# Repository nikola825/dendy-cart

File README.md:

# Programmable cartridge for Dendy-style consoles

Programmable PLD-based cartrige for Dendy-like consoles.

## Features
1. 1MB of SRAM for use as PRG ROM or PRG RAM
2. 1MB of SRAM for use as CHR ROM or CHR RAM
3. Atmel ATF1508 CPLD for glue logic, mapper implementation and flashing
4. LM66100 and a CR2032 battery holder to allow RAM to act as non-volatile storage
5. JTAG header for CPLD flashing

## Tooling
Makefile and linker configuration for writing programs
Pattern table generator script to generate pattern table contents from bitmaps

## Repo contents
cart - Kicad project and BOM
verilog - Verilog code for the ATF1508 CPLD
6502_development/demo_program - demo code for writing programs
6502_development/bmptransform - python script to generate pattern table contents from bmp images

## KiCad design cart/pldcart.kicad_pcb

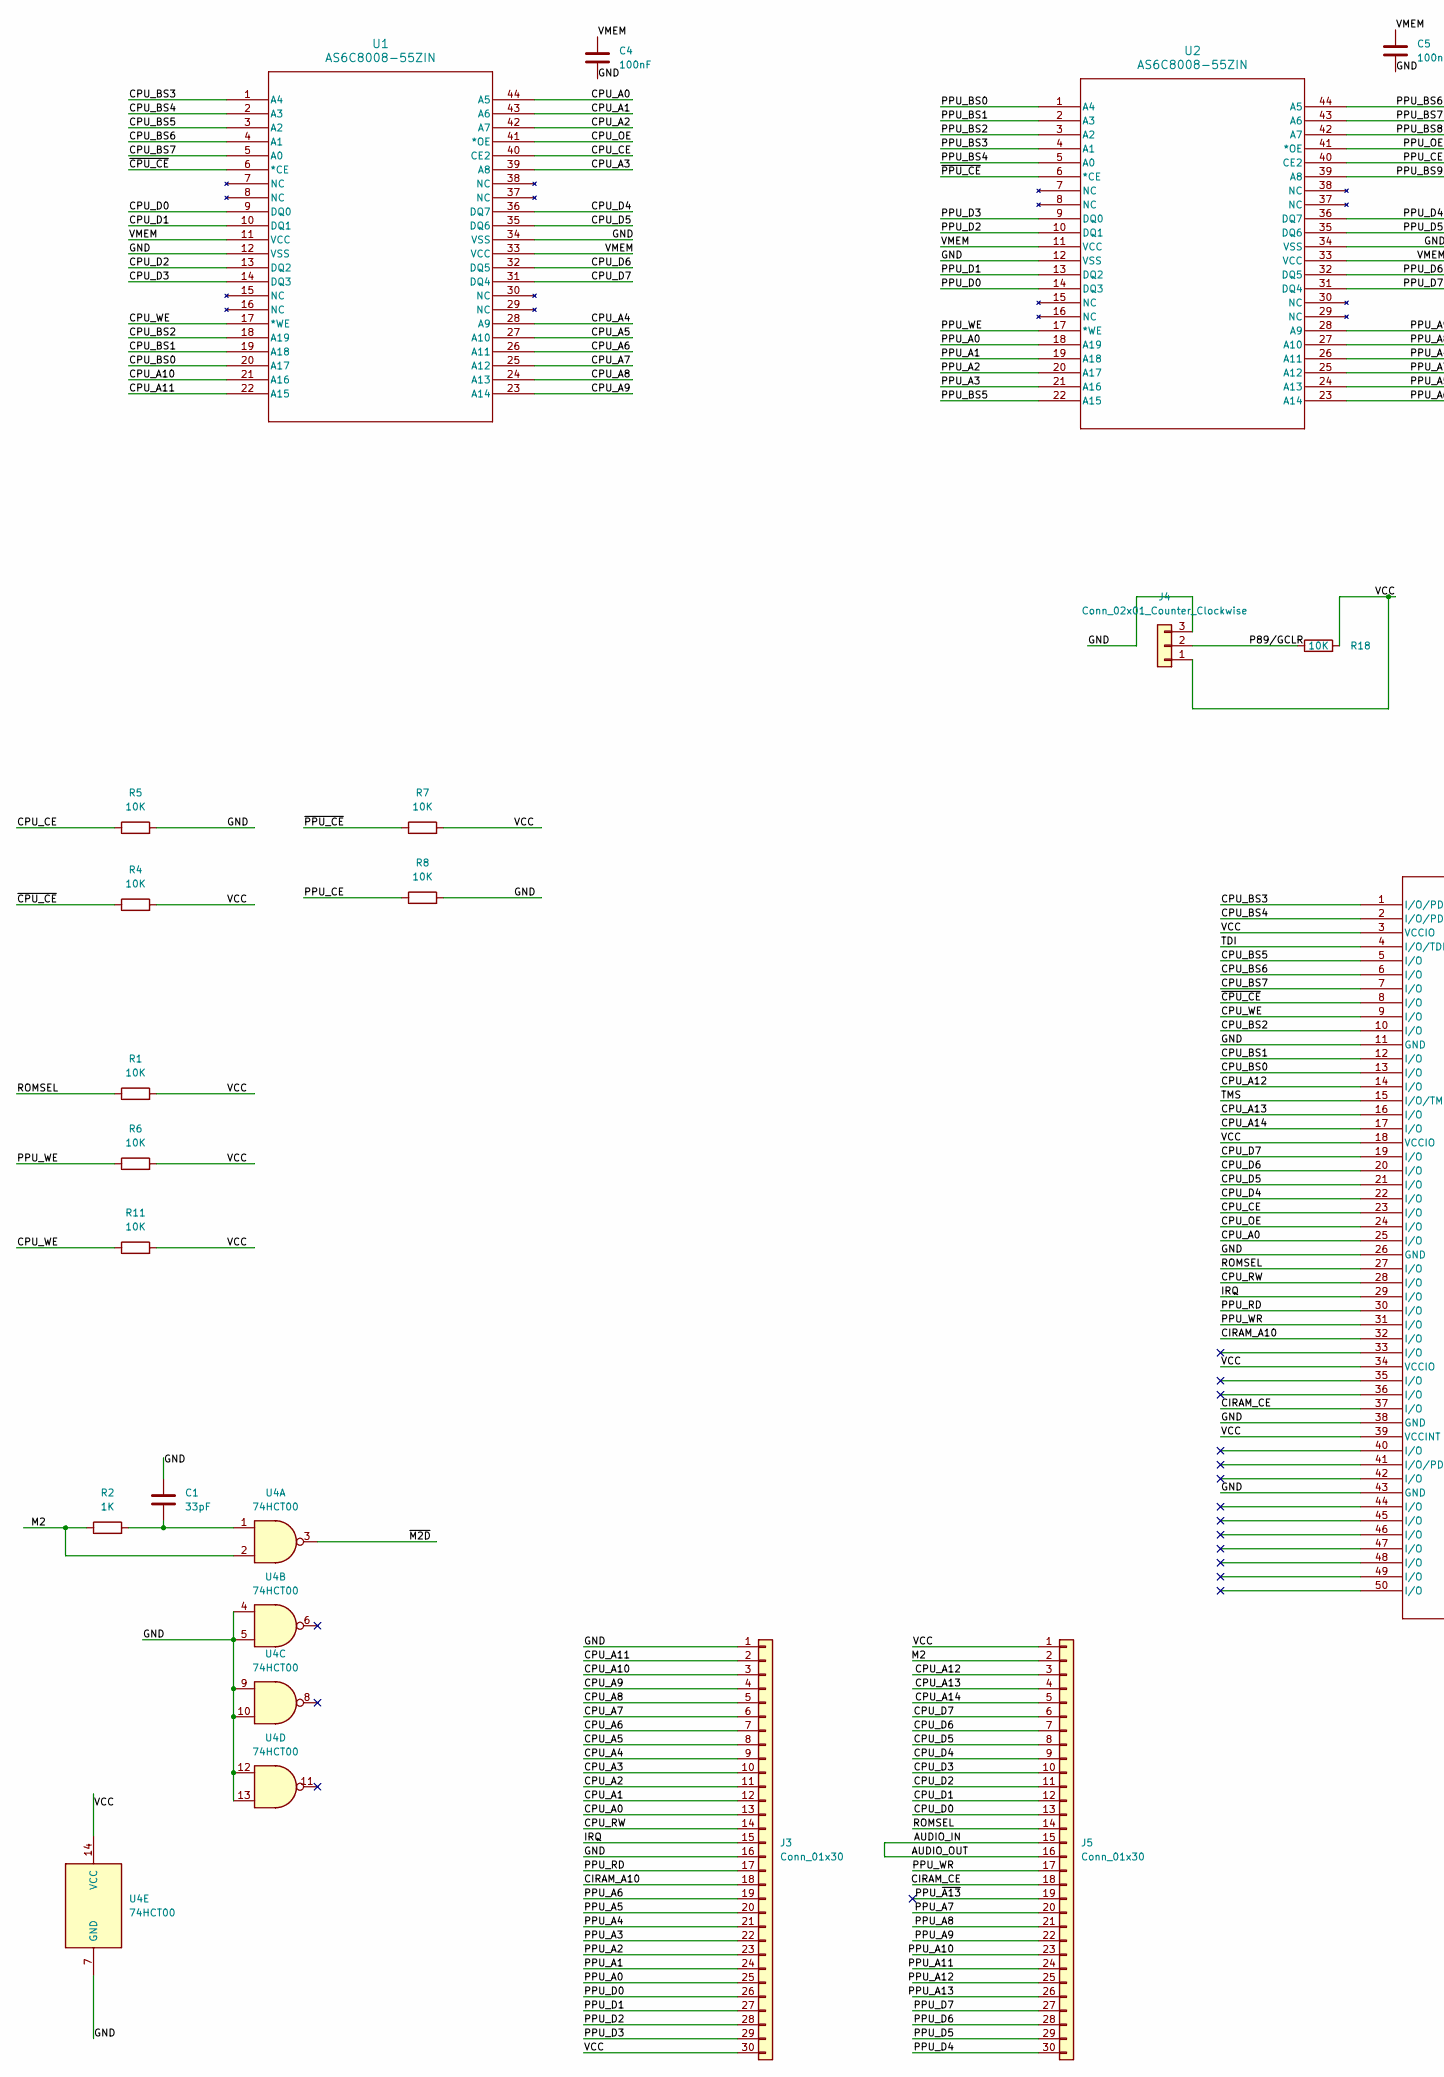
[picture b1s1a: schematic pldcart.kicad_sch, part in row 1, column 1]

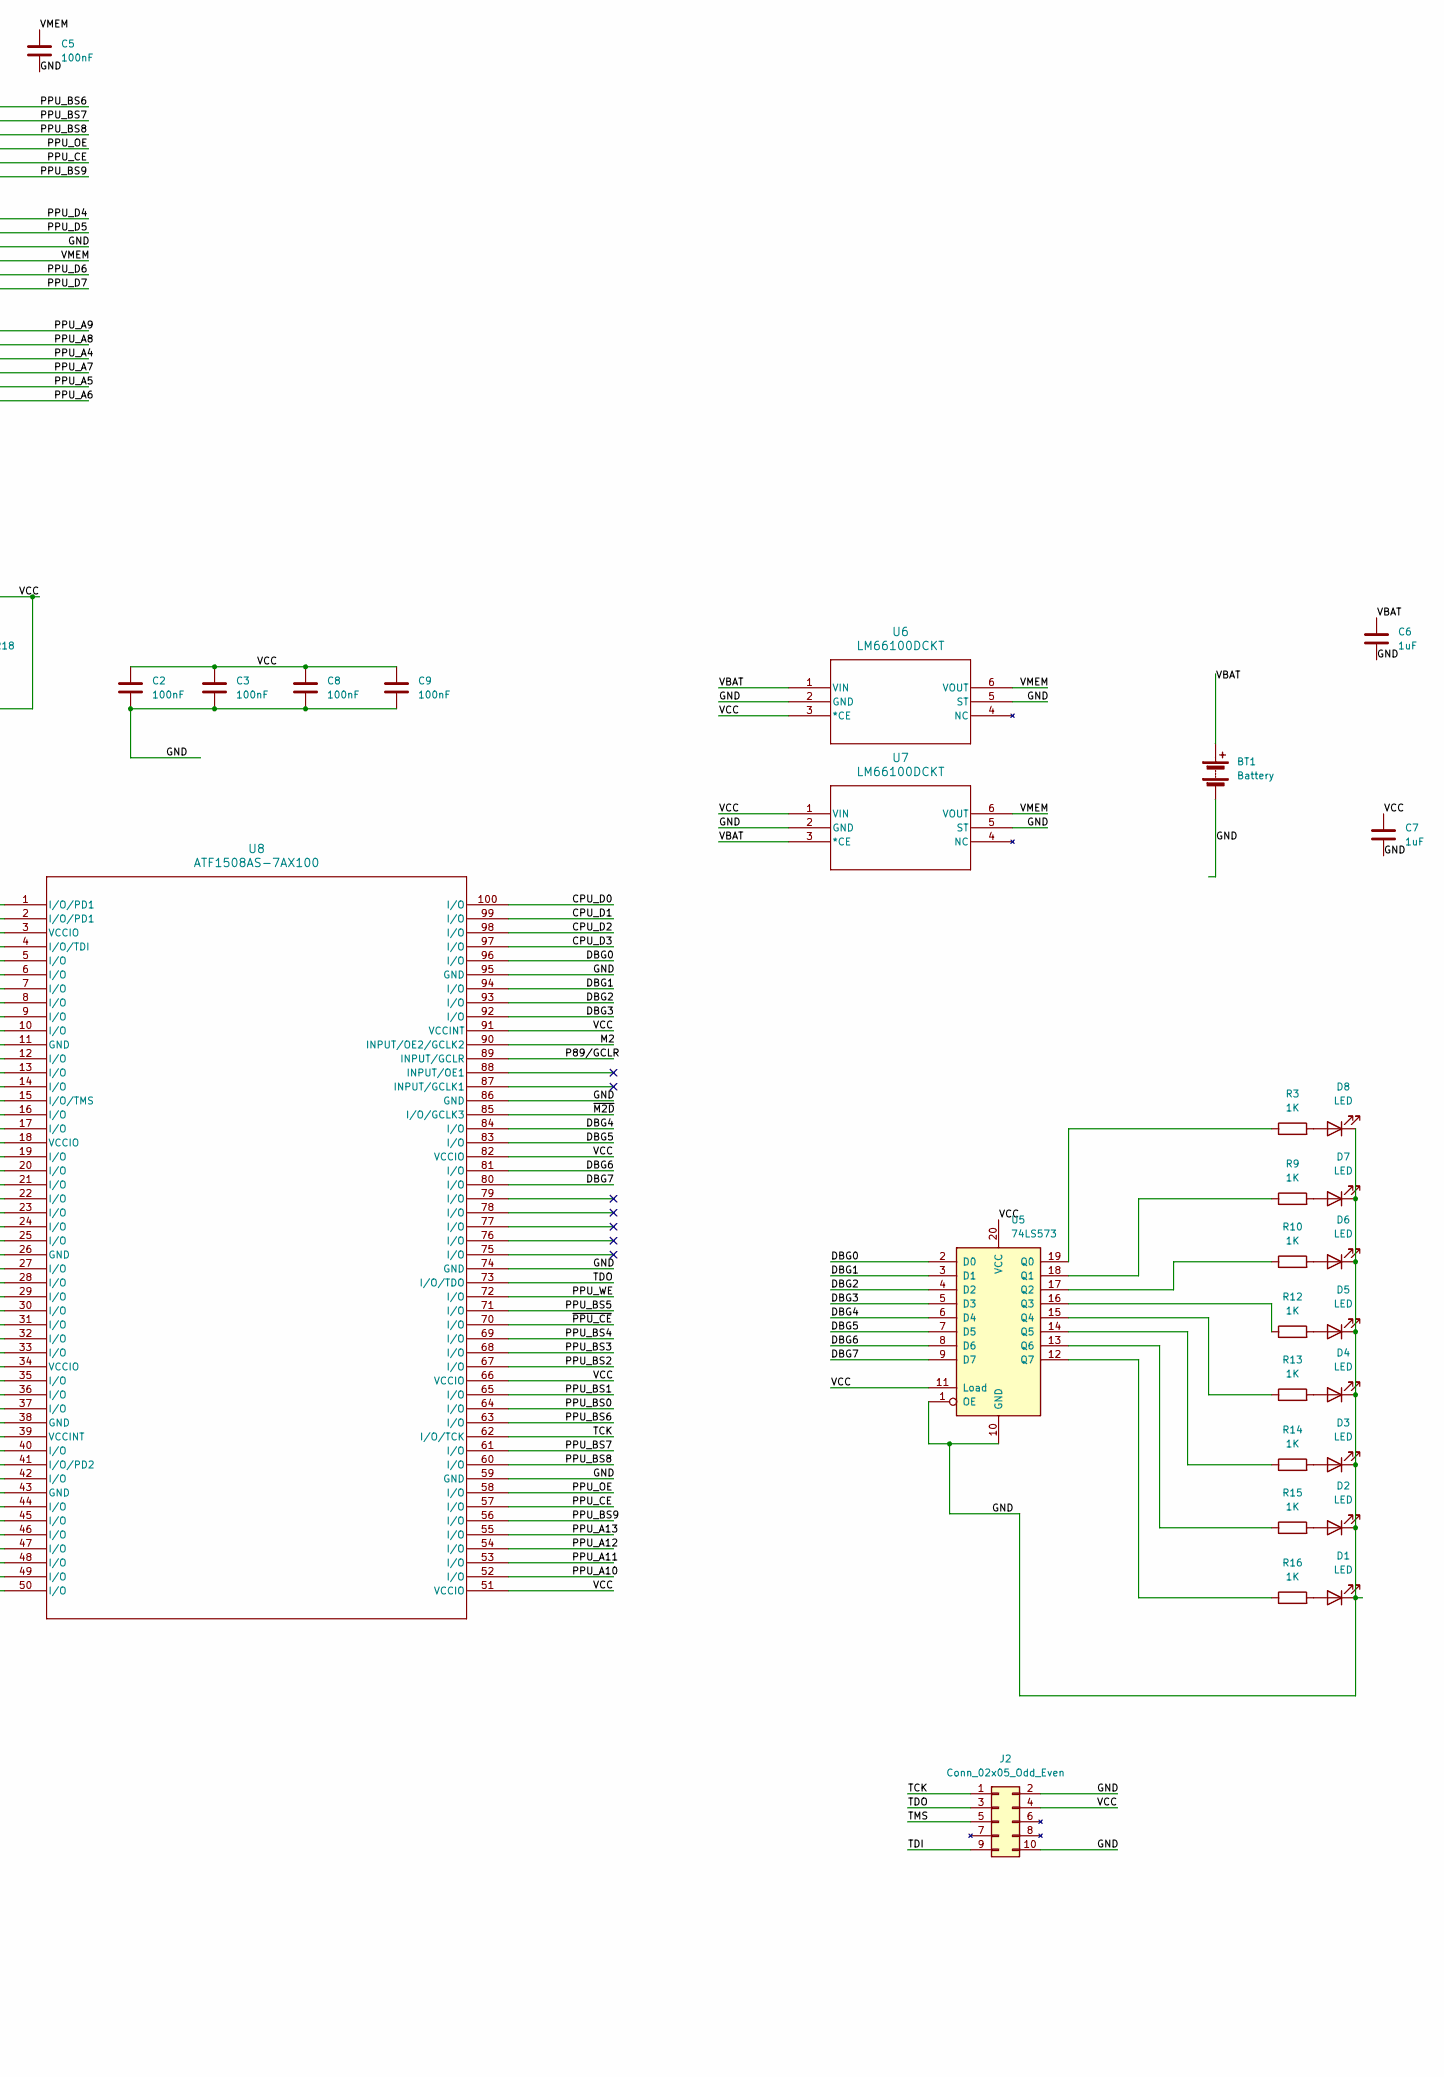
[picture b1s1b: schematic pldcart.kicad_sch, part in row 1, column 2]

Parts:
BT1: Battery; BatteryHolder_Keystone_103_1x20mm
C1: 33pF; C_0603_1608Metric
C2, C3, C4, C5, C8, C9: 100nF; C_0603_1608Metric
C6, C7: 1uF; C_0805_2012Metric
D1, D2, D3, D4, D5, D6, D7, D8: LED; LED_0603_1608Metric
J2: Conn_02x05_Odd_Even; PinHeader_2x05_P2.54mm_Vertical
J3, J5: Conn_01x30; PinHeader_1x30_P2.54mm_Vertical
J4: Conn_02x01_Counter_Clockwise; PinHeader_1x03_P2.54mm_Vertical
R1, R4, R5, R6, R7, R8, R11, R18: 10K; R_0603_1608Metric
R2, R3, R9, R10, R12, R13, R14, R15, R16: 1K; R_0603_1608Metric
U1, U2: AS6C8008-55ZIN; TSOP-II-44_10.16x18.41mm_P0.8mm
U4: 74HCT00; TSSOP-14_4.4x5mm_P0.65mm
U5: 74LS573; TSSOP-20_4.4x6.5mm_P0.65mm
U6, U7: LM66100DCKT; SOT-363_SC-70-6
U8: ATF1508AS-7AX100; TQFP-100_14x14mm_P0.5mm

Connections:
/AUDIO_IN: J5.15, J5.16
/CIRAM_A10: J3.18, U8.32 (I/O)
/CIRAM_CE: J5.18, U8.37 (I/O)
/CPU_A0: J3.13, U1.44 (A5), U8.25 (I/O)
/CPU_A1: J3.12, U1.43 (A6)
/CPU_A2: J3.11, U1.42 (A7)
/CPU_A3: J3.10, U1.39 (A8)
/CPU_A4: J3.9, U1.28 (A9)
/CPU_A5: J3.8, U1.27 (A10)
/CPU_A6: J3.7, U1.26 (A11)
/CPU_A7: J3.6, U1.25 (A12)
/CPU_A8: J3.5, U1.24 (A13)
/CPU_A9: J3.4, U1.23 (A14)
/CPU_A10: J3.3, U1.21 (A16)
/CPU_A11: J3.2, U1.22 (A15)
/CPU_A12: J5.3, U8.14 (I/O)
/CPU_A13: J5.4, U8.16 (I/O)
/CPU_A14: J5.5, U8.17 (I/O)
/CPU_BS0: U1.20 (A17), U8.13 (I/O)
/CPU_BS1: U1.19 (A18), U8.12 (I/O)
/CPU_BS2: U1.18 (A19), U8.10 (I/O)
/CPU_BS3: U1.1 (A4), U8.1 (I/O/PD1)
/CPU_BS4: U1.2 (A3), U8.2 (I/O/PD1)
/CPU_BS5: U1.3 (A2), U8.5 (I/O)
/CPU_BS6: U1.4 (A1), U8.6 (I/O)
/CPU_BS7: U1.5 (A0), U8.7 (I/O)
/CPU_CE: R5.1, U1.40 (CE2), U8.23 (I/O)
/CPU_D0: J5.13, U1.9 (DQ0), U8.100 (I/O)
/CPU_D1: J5.12, U1.10 (DQ1), U8.99 (I/O)
/CPU_D2: J5.11, U1.13 (DQ2), U8.98 (I/O)
/CPU_D3: J5.10, U1.14 (DQ3), U8.97 (I/O)
/CPU_D4: J5.9, U1.36 (DQ7), U8.22 (I/O)
/CPU_D5: J5.8, U1.35 (DQ6), U8.21 (I/O)
/CPU_D6: J5.7, U1.32 (DQ5), U8.20 (I/O)
/CPU_D7: J5.6, U1.31 (DQ4), U8.19 (I/O)
/CPU_OE: U1.41 (*OE), U8.24 (I/O)
/CPU_RW: J3.14, U8.28 (I/O)
/CPU_WE: R11.1, U1.17 (*WE), U8.9 (I/O)
/DBG0: U5.2 (D0), U8.96 (I/O)
/DBG1: U5.3 (D1), U8.94 (I/O)
/DBG2: U5.4 (D2), U8.93 (I/O)
/DBG3: U5.5 (D3), U8.92 (I/O)
/DBG4: U5.6 (D4), U8.84 (I/O)
/DBG5: U5.7 (D5), U8.83 (I/O)
/DBG6: U5.8 (D6), U8.81 (I/O)
/DBG7: U5.9 (D7), U8.80 (I/O)
/GND: BT1.2 (-), C1.1, C2.2, C3.2, C4.2, C5.2, C6.2, C7.2, C8.2, C9.2, D1.1 (K), D2.1 (K), D3.1 (K), D4.1 (K), D5.1 (K), D6.1 (K), D7.1 (K), D8.1 (K), J2.2, J2.10, J3.1, J3.16, J4.3, R5.2, R8.2, U1.12 (VSS), U1.34 (VSS), U2.12 (VSS), U2.34 (VSS), U4.4, U4.5, U4.7 (GND), U4.9, U4.10, U4.12, U4.13, U5.1 (OE), U5.10 (GND), U6.2 (GND), U6.5 (ST), U7.2 (GND), U7.5 (ST), U8.11 (GND), U8.26 (GND), U8.38 (GND), U8.43 (GND), U8.59 (GND), U8.74 (GND), U8.86 (GND), U8.95 (GND)
/IRQ: J3.15, U8.29 (I/O)
/M2: J5.2, R2.1, U4.2, U8.90 (INPUT/OE2/GCLK2)
/P89/GCLR: J4.2, R18.1, U8.89 (INPUT/GCLR)
/PPU_A0: J3.25, U2.18 (A19)
/PPU_A1: J3.24, U2.19 (A18)
/PPU_A2: J3.23, U2.20 (A17)
/PPU_A3: J3.22, U2.21 (A16)
/PPU_A4: J3.21, U2.26 (A11)
/PPU_A5: J3.20, U2.24 (A13)
/PPU_A6: J3.19, U2.23 (A14)
/PPU_A7: J5.20, U2.25 (A12)
/PPU_A8: J5.21, U2.27 (A10)
/PPU_A9: J5.22, U2.28 (A9)
/PPU_A10: J5.23, U8.52 (I/O)
/PPU_A11: J5.24, U8.53 (I/O)
/PPU_A12: J5.25, U8.54 (I/O)
/PPU_A13: J5.26, U8.55 (I/O)
/PPU_BS0: U2.1 (A4), U8.64 (I/O)
/PPU_BS1: U2.2 (A3), U8.65 (I/O)
/PPU_BS2: U2.3 (A2), U8.67 (I/O)
/PPU_BS3: U2.4 (A1), U8.68 (I/O)
/PPU_BS4: U2.5 (A0), U8.69 (I/O)
/PPU_BS5: U2.22 (A15), U8.71 (I/O)
/PPU_BS6: U2.44 (A5), U8.63 (I/O)
/PPU_BS7: U2.43 (A6), U8.61 (I/O)
/PPU_BS8: U2.42 (A7), U8.60 (I/O)
/PPU_BS9: U2.39 (A8), U8.56 (I/O)
/PPU_CE: R8.1, U2.40 (CE2), U8.57 (I/O)
/PPU_D0: J3.26, U2.14 (DQ3)
/PPU_D1: J3.27, U2.13 (DQ2)
/PPU_D2: J3.28, U2.10 (DQ1)
/PPU_D3: J3.29, U2.9 (DQ0)
/PPU_D4: J5.30, U2.36 (DQ7)
/PPU_D5: J5.29, U2.35 (DQ6)
/PPU_D6: J5.28, U2.32 (DQ5)
/PPU_D7: J5.27, U2.31 (DQ4)
/PPU_OE: U2.41 (*OE), U8.58 (I/O)
/PPU_RD: J3.17, U8.30 (I/O)
/PPU_WE: R6.1, U2.17 (*WE), U8.72 (I/O)
/PPU_WR: J5.17, U8.31 (I/O)
/PPU_~A13: J5.19
/ROMSEL: J5.14, R1.1, U8.27 (I/O)
/TCK: J2.1, U8.62 (I/O/TCK)
/TDI: J2.9, U8.4 (I/O/TDI)
/TDO: J2.3, U8.73 (I/O/TDO)
/TMS: J2.5, U8.15 (I/O/TMS)
/VBAT: BT1.1 (+), C6.1, U6.1 (VIN), U7.3 (*CE)
/VCC: C2.1, C3.1, C7.1, C8.1, C9.1, J2.4, J3.30, J4.1, J5.1, R1.2, R4.2, R6.2, R7.2, R11.2, R18.2, U4.14 (VCC), U5.11 (Load), U5.20 (VCC), U6.3 (*CE), U7.1 (VIN), U8.3 (VCCIO), U8.18 (VCCIO), U8.34 (VCCIO), U8.39 (VCCINT), U8.51 (VCCIO), U8.66 (VCCIO), U8.82 (VCCIO), U8.91 (VCCINT)
/VMEM: C4.1, C5.1, U1.11 (VCC), U1.33 (VCC), U2.11 (VCC), U2.33 (VCC), U6.6 (VOUT), U7.6 (VOUT)
/~CPU_CE: R4.1, U1.6 (*CE), U8.8 (I/O)
/~M2D: U4.3, U8.85 (I/O/GCLK3)
/~PPU_CE: R7.1, U2.6 (*CE), U8.70 (I/O)
unnamed: C1.2, R2.2, U4.1
unnamed: D1.2 (A), R16.2
unnamed: D2.2 (A), R15.2
unnamed: D3.2 (A), R14.2
unnamed: D4.2 (A), R13.2
unnamed: D5.2 (A), R12.2
unnamed: D6.2 (A), R10.2
unnamed: D7.2 (A), R9.2
unnamed: D8.2 (A), R3.2
unnamed: R3.1, U5.19 (Q0)
unnamed: R9.1, U5.18 (Q1)
unnamed: R10.1, U5.17 (Q2)
unnamed: R12.1, U5.16 (Q3)
unnamed: R13.1, U5.15 (Q4)
unnamed: R14.1, U5.14 (Q5)
unnamed: R15.1, U5.13 (Q6)
unnamed: R16.1, U5.12 (Q7)

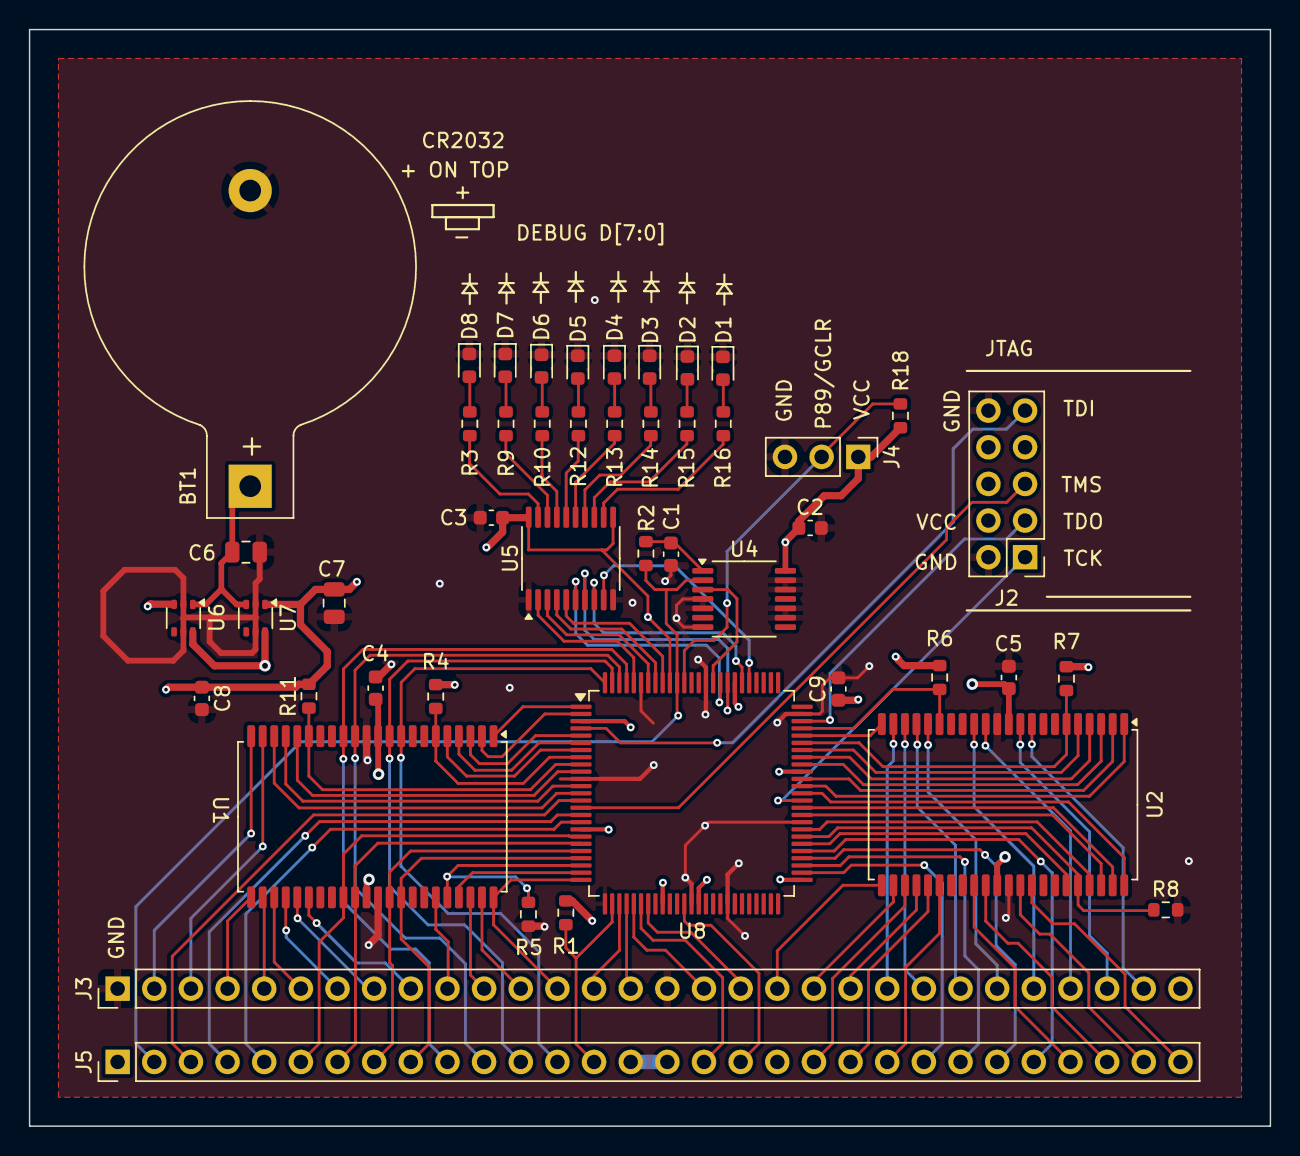
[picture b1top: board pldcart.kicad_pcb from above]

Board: 4 copper layers, 86.0 x 76.0 mm, 46 parts (0 on the bottom side), 115 nets.

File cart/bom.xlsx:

|  |  | xxxx xxxx xxxxx xxPCS BOM (Sample Bill of Materials)
Item # | *Designator | *Qty | Manufacturer | *Mfg Part # | Description / Value | *Package/Footprint | Type | Your Instructions / Notes
1 | C1 | 1 | Don’t care | Don’t care | CAP CER 33pF 16V C0G 0603 | 0603 | SMD | Don’t care about model/manufacturer, just make sure it fits description
2 | C2, C3, C4, C5, C8, C9 | 6 | Don’t care | Don’t care | CAP CER 100nF 16V X7R 0603 | 0603 | SMD | Don’t care about model/manufacturer, just make sure it fits description
3 | C6, C7 | 2 | Don’t care | Don’t care | CAP CER 1uF 16V X7R 0805 | 0805 | SMD | Don’t care about model/manufacturer, just make sure it fits description
4 | D1, D2, D3, D4, D5, D6, D7, D8 | 8 | Foshan NationStar | NCD0603R1 | LED SMD Red 2V 20ma 0603 | 0603 | SMD
5 | R1, R4, R5, R6, R7, R8, R11, R18 | 8 | Don’t care | Don’t care | RES 10K OHM 0.1W 1% 0603 SMD | 0603 | SMD | Don’t care about model/manufacturer, just make sure it fits description
6 | R2, R3, R9, R10, R12, R13, R14, R15, R16 | 9 | Don’t care | Don’t care | RES 1K OHM 0.1W 1% 0603 SMD | 0603 | SMD | Don’t care about model/manufacturer, just make sure it fits description
7 | U1, U2 | 2 | Alliance Memory | AS6C8008-55ZIN | SRAM - Asynchronous Memory IC 8Mbit Parallel 55 ns 44-TSOP II | 44pin TSOP II | SMD
8 | U4 | 1 | Texas Instruments | SN74HCT00PWR | IC GATE NAND 4CH 2-INP 14TSSOP | 14-TSSOP | SMD
9 | U5 | 1 | Texas Instruments | SN74HCT573PWR | D-Type Transparent Latch 1 Channel 8:8 IC Tri-State 20-TSSOP | 20-TSSOP | SMD
10 | U6, U7 | 2 | Texas Instruments | LM66100DCKT | OR Controller P-Channel 1:1 SC-70-6 | 6-TSSOP, SC-88, SOT-363 | SMD
11 | U8 | 1 | Microchip Technology | ATF1508AS-7AX100 | TQFP-100(14x14) Programmable Logic Device CPLD | TQFP-100(14x14) | SMD
12 | J5/J3 | 1 | Sullins | ECC30MMVD-S189/4548247 | 60 Position Male Connector Fits Female Edgecards Gold 0.100" (2.54mm) | TH 2.54x5.08 | TH
Need a quick and accurante quote? Need an efficient production? Please read SMT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
Click for Instructions on How to Create a BOM
